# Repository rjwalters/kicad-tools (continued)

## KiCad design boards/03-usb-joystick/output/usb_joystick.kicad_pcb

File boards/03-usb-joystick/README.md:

# USB Joystick Controller Demo

This demo demonstrates the kicad-tools autorouter by routing a USB game controller PCB
with mixed signal types: USB differential pairs, analog inputs, and digital I/O.

## Quick Start

```bash
# One-command build (recommended)
kct build boards/03-usb-joystick

# Or run specific steps
kct build boards/03-usb-joystick --step schematic
kct build boards/03-usb-joystick --step pcb
kct build boards/03-usb-joystick --step route
kct build boards/03-usb-joystick --step verify

# Preview what would happen
kct build boards/03-usb-joystick --dry-run
```

## Circuit Overview

```
                          +------------------+
    +--------+            |                  |
    | USB-C  |---D+/D--->| MCU (32-pin QFP) |<---[Y1 Crystal]
    |  J1    |---VBUS--->|                  |
    +--------+            |   ATmega32U4    |<---[C1-C4 Decoupling]
                          |                  |
                          +--------+---------+
                                   |
          +------------------------+------------------------+
          |            |           |           |            |
      +---+---+   +----+----+  +---+---+   +---+---+   +---+---+
      | JOY_X |   | JOY_Y   |  | BTN1  |   | BTN2  |   | BTN3  |
      +-------+   +---------+  +-------+   +-------+   +-------+
         Analog Joystick              Tactile Buttons
```

## Components

| Reference | Description | Footprint |
|-----------|-------------|-----------|
| U1 | Microcontroller (ATmega32U4-style) | TQFP-32 7x7mm |
| J1 | USB Type-C Connector | USB-C Receptacle |
| J2 | 2-axis Analog Joystick | 5-pin module |
| SW1-SW4 | Tactile Buttons | 6x6mm SMD |
| Y1 | 16MHz Crystal | HC49 Vertical |
| C1-C4 | Decoupling Capacitors (100nF) | 0402 SMD |

## Signal Types

This design demonstrates routing of different signal classes:

### USB Signals (High Priority)
- **USB_D+, USB_D-**: Differential pair, should be length-matched
- **VBUS**: 5V power from USB host
- **USB_CC1, USB_CC2**: Configuration channel for USB-C

### Analog Signals
- **JOY_X, JOY_Y**: Analog joystick axis outputs (0-VCC)
- **JOY_BTN**: Joystick button (active low)

### Digital Signals
- **BTN1-BTN4**: Button inputs (active low with GND)
- **XTAL1, XTAL2**: Crystal oscillator connections

### Power
- **VCC**: 3.3V/5V regulated power
- **GND**: Ground reference
- **VBUS**: USB 5V input

## Files

| File | Description |
|------|-------------|
| `generate_pcb.py` | Script to generate the unrouted PCB file |
| `generate_schematic.py` | Script to generate the schematic file |
| `route_demo.py` | Thin wrapper that delegates to `generate_design.py:route_pcb()` (Issue #3308) |
| `generate_design.py` | End-to-end design flow (schematic + PCB + route + export); owns the canonical routing recipe |
| `output/usb_joystick.kicad_sch` | Generated schematic |
| `output/usb_joystick.kicad_pcb` | Generated unrouted PCB |
| `output/usb_joystick_routed.kicad_pcb` | Routed PCB output |

## Advanced: Manual Build

For more control over individual steps, you can run Python scripts directly. See [Prerequisites](../README.md#prerequisites-for-manual-build) for environment setup.

### Step 1: Generate the Schematic

```bash
# From repository root (default output)
uv run python boards/03-usb-joystick/generate_schematic.py

# Or specify an output directory (auto-appends filename)
uv run python boards/03-usb-joystick/generate_schematic.py output/

# Or specify an explicit file path
uv run python boards/03-usb-joystick/generate_schematic.py output/usb_joystick.kicad_sch
```

Creates `output/usb_joystick.kicad_sch` with all components and wiring.

### Step 2: Generate the PCB

```bash
# From repository root
uv run python boards/03-usb-joystick/generate_pcb.py
```

Creates `output/usb_joystick.kicad_pcb` with all components placed and nets defined.

### Step 3: Run the Autorouter

```bash
# From repository root
uv run python boards/03-usb-joystick/route_demo.py
```

Issue #3308 (June 2026): `route_demo.py` is a thin wrapper that
delegates to `generate_design.py:route_pcb()`.  This guarantees the
demo recipe and the end-to-end build recipe share a single
implementation -- they cannot drift again.  `kct build --step route`
also invokes `route_demo.py` (see `_run_step_route` in
`src/kicad_tools/cli/build_cmd.py`), so all three entry points
(``route_demo.py``, ``kct build --step route``, ``generate_design.py``)
now produce the same routed output.

This:
1. Loads the unrouted PCB
2. Configures net classes (USB gets high priority)
3. Routes signal nets (power nets are skipped, assuming planes)
4. Saves the result to `output/usb_joystick_routed.kicad_pcb`

**Note:** This is a challenging routing problem with a dense 32-pin QFP and multiple
signal types. The autorouter demonstrates its capabilities but may not complete all
routes on a 2-layer board. This is realistic for complex designs requiring manual
intervention or additional layers.

### Step 4: View in KiCad (Optional)

Open `usb_joystick_routed.kicad_pcb` in KiCad to visualize the routes.

## Net Class Configuration

The demo configures net classes for priority-based routing:

```python
net_class_map = create_net_class_map(
    power_nets=["VCC", "VBUS", "GND"],  # Highest priority
    high_speed_nets=["USB_D+", "USB_D-"],  # USB differential pair
    clock_nets=["XTAL1", "XTAL2"],  # Crystal oscillator
)
```

This ensures:
1. Power nets route first (if not skipped)
2. USB differential pair routes early for best path
3. Crystal traces stay short
4. Button/joystick signals route last

## Design Considerations

### USB Routing
- D+ and D- should be routed as a differential pair
- Keep traces short and matched in length
- Avoid sharp bends (use 45-degree angles)

### Analog Signals
- JOY_X and JOY_Y carry analog voltages
- Keep away from high-speed digital signals
- Consider guard traces if noise is an issue

### Crystal Routing
- XTAL1 and XTAL2 should be short
- Place crystal close to MCU pins
- Avoid routing other signals under crystal

### Decoupling Capacitors
- C1-C3 placed close to MCU VCC pins
- C4 on VBUS near USB connector
- Short traces to GND plane

## Customization

### Change Design Rules

```python
rules = DesignRules(
    grid_resolution=0.25,  # Routing grid
    trace_width=0.25,  # Default trace width
    trace_clearance=0.15,  # Minimum clearance
    via_drill=0.3,  # Via drill diameter
    via_diameter=0.6,  # Via pad diameter
)
```

### Route Power Nets

By default, VCC/GND/VBUS are skipped (assuming copper pours). To route them:

```python
skip_nets = []  # Route everything
```

### Adjust Component Placement

Edit `generate_pcb.py` to modify:
- Board dimensions
- Component positions
- Pin assignments

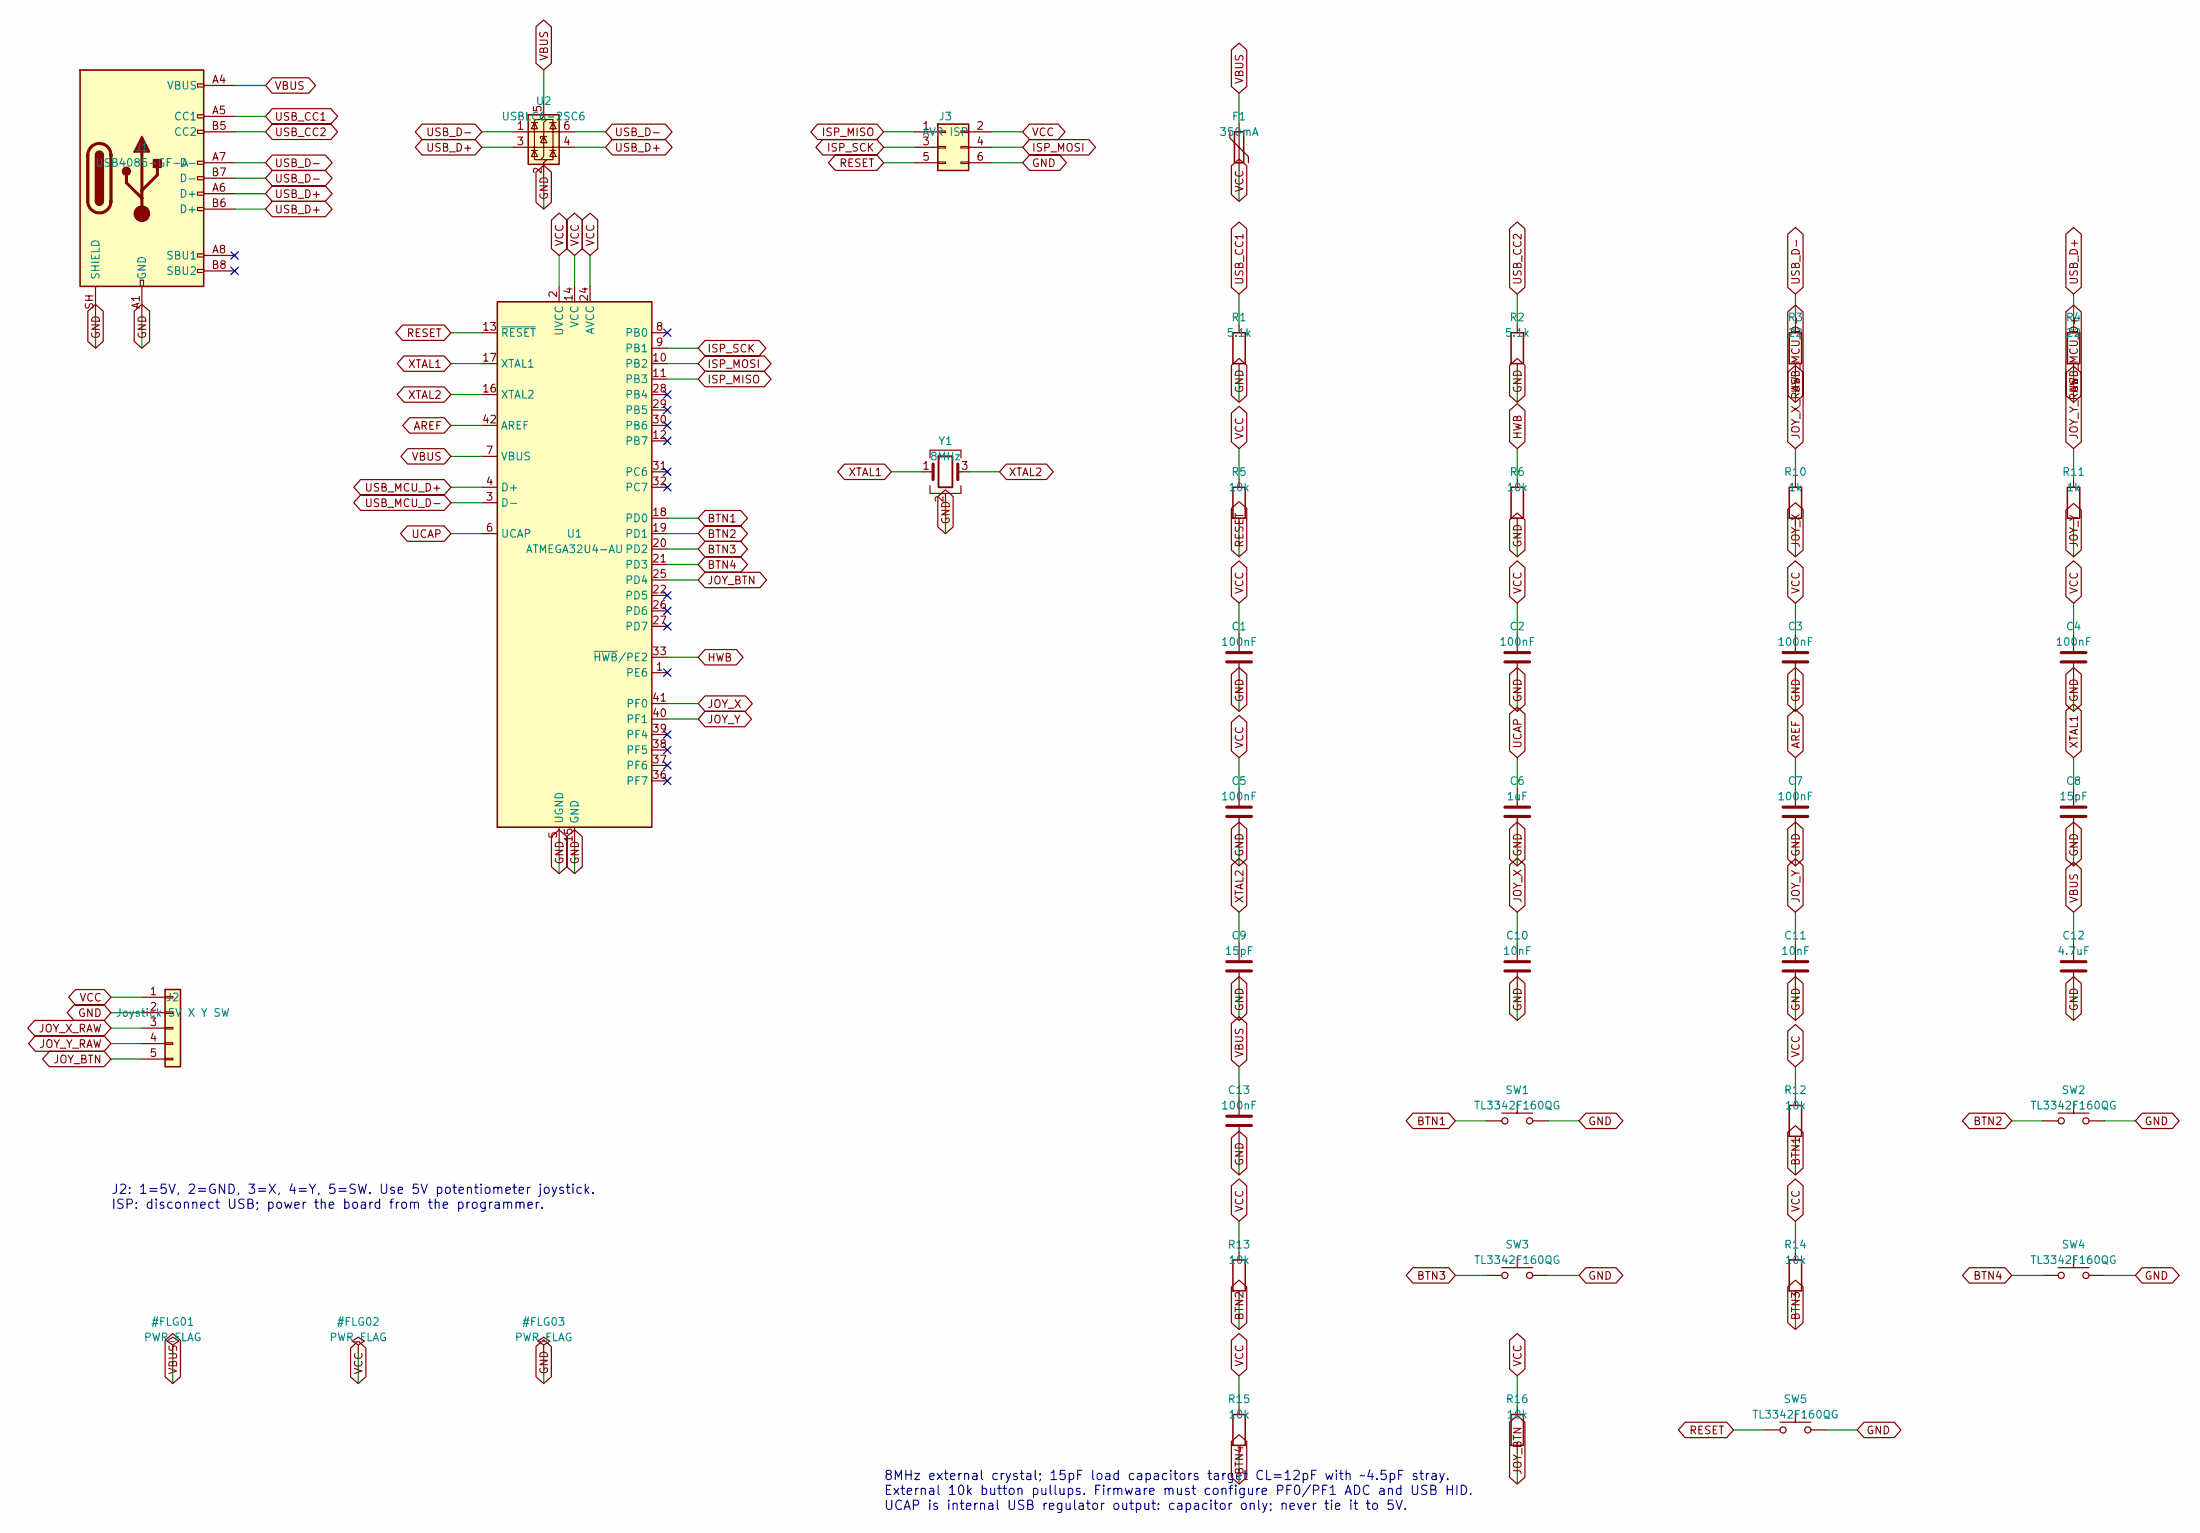
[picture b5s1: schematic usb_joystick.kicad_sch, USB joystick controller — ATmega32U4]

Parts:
C1, C2, C3, C4, C5, C7, C13: 100nF; C_0603_1608Metric; MPN GRM188R71C104KA01D; LCSC C45000
C6: 1uF; C_0603_1608Metric; MPN GRM188R71A105KA61D; LCSC C97888
C8, C9: 15pF; C_0603_1608Metric; MPN GRM1885C1H150JA01D; LCSC C71651
C10, C11: 10nF; C_0603_1608Metric; MPN GRM188R71H103KA01D; LCSC C77053
C12: 4.7uF; C_0603_1608Metric; MPN GRM188R61A475KE15D; LCSC C71633
F1: 350mA; Fuse_1206_3216Metric; MPN 1206L035/16YR; LCSC C126817
J1: USB4085-GF-A; USB_C_Receptacle_GCT_USB4085; MPN USB4085-GF-A; LCSC C7095263
J2: Joystick 5V X Y SW; JST_PH_S5B-PH-SM4-TB_1x05-1MP_P2.00mm_Horizontal; MPN S5B-PH-SM4-TB(LF)(SN); LCSC C265104
J3: AVR ISP; Samtec_TSM-103-01-T-DV; MPN TSM-103-01-T-DV-P-TR; LCSC C21285200
R1, R2: 5.1k; R_0603_1608Metric; MPN RC0603FR-075K1L; LCSC C105580
R3, R4: 22; R_0402_1005Metric; MPN RC0402FR-0722RL; LCSC C114765
R5, R6, R12, R13, R14, R15, R16: 10k; R_0603_1608Metric; MPN RC0603FR-0710KL; LCSC C98220
R10, R11: 1k; R_0603_1608Metric; MPN RC0603FR-071KL; LCSC C22548
SW1, SW2, SW3, SW4, SW5: TL3342F160QG; SW_SPST_TL3342; MPN TL3342F160QG; LCSC C2886898
U1: ATMEGA32U4-AU; TQFP-44_10x10mm_P0.8mm; MPN ATMEGA32U4-AU; LCSC C44854
U2: USBLC6-2SC6; SOT-23-6; MPN USBLC6-2SC6; LCSC C7519
Y1: 8MHz; Crystal_SMD_3225-4Pin_3.2x2.5mm; MPN ECS-80-12-33-JGN-TR; LCSC C2442665

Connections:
AREF: C7.1, U1.42 (AREF)
BTN1: R12.2, SW1.1, U1.18 (PD0)
BTN2: R13.2, SW2.1, U1.19 (PD1)
BTN3: R14.2, SW3.1, U1.20 (PD2)
BTN4: R15.2, SW4.1, U1.21 (PD3)
GND: C1.2, C2.2, C3.2, C4.2, C5.2, C6.2, C7.2, C8.2, C9.2, C10.2, C11.2, C12.2, C13.2, J1.A1 (GND), J1.A12 (GND), J1.B1 (GND), J1.B12 (GND), J1.SH (SHIELD), J2.2, J3.6, R1.2, R2.2, R6.2, SW1.2, SW2.2, SW3.2, SW4.2, SW5.2, U1.5 (UGND), U1.15 (GND), U1.23 (GND), U1.35 (GND), U1.43 (GND), U2.2 (GND), Y1.2 (G), Y1.4 (G)
HWB: R6.1, U1.33 (~HWB/PE2)
ISP_MISO: J3.1, U1.11 (PB3)
ISP_MOSI: J3.4, U1.10 (PB2)
ISP_SCK: J3.3, U1.9 (PB1)
JOY_BTN: J2.5, R16.2, U1.25 (PD4)
JOY_X: C10.1, R10.2, U1.41 (PF0)
JOY_X_RAW: J2.3, R10.1
JOY_Y: C11.1, R11.2, U1.40 (PF1)
JOY_Y_RAW: J2.4, R11.1
RESET: J3.5, R5.2, SW5.1, U1.13 (~RESET)
UCAP: C6.1, U1.6 (UCAP)
USB_CC1: J1.A5 (CC1), R1.1
USB_CC2: J1.B5 (CC2), R2.1
USB_D+: J1.A6 (D+), J1.B6 (D+), R4.1, U2.3 (I/O2), U2.4 (I/O2)
USB_D-: J1.A7 (D-), J1.B7 (D-), R3.1, U2.1 (I/O1), U2.6 (I/O1)
USB_MCU_D+: R4.2, U1.4 (D+)
USB_MCU_D-: R3.2, U1.3 (D-)
VBUS: C12.1, C13.1, F1.1, J1.A4 (VBUS), J1.A9 (VBUS), J1.B4 (VBUS), J1.B9 (VBUS), U1.7 (VBUS), U2.5 (VBUS)
VCC: C1.1, C2.1, C3.1, C4.1, C5.1, F1.2, J2.1, J3.2, R5.1, R12.1, R13.1, R14.1, R15.1, R16.1, U1.2 (UVCC), U1.14 (VCC), U1.24 (AVCC), U1.34 (VCC), U1.44 (AVCC)
XTAL1: C8.1, U1.17 (XTAL1), Y1.1
XTAL2: C9.1, U1.16 (XTAL2), Y1.3

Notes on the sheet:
J2: 1=5V, 2=GND, 3=X, 4=Y, 5=SW. Use 5V potentiometer joystick. ISP: disconnect USB; power the board from the programmer.
8MHz external crystal; 15pF load capacitors target CL=12pF with ~4.5pF stray. External 10k button pullups. Firmware must configure PF0/PF1 ADC and USB HID. UCAP is internal USB regulator output: capacitor only; never tie it to 5V.

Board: 4 copper layers, 38 parts (0 on the bottom side), 27 nets, no tracks yet.

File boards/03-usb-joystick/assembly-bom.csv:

Reference,Value,Manufacturer,MPN,Footprint
U1,ATMEGA32U4-AU,Microchip,ATMEGA32U4-AU,Package_QFP:TQFP-44_10x10mm_P0.8mm
J1,USB4085-GF-A,GCT,USB4085-GF-A,Connector_USB:USB_C_Receptacle_GCT_USB4085
U2,USBLC6-2SC6,STMicroelectronics,USBLC6-2SC6,Package_TO_SOT_SMD:SOT-23-6
F1,350mA,Littelfuse,1206L035/16YR,Fuse:Fuse_1206_3216Metric
Y1,8MHz,ECS,ECS-80-12-33-JGN-TR,Crystal:Crystal_SMD_3225-4Pin_3.2x2.5mm
J2,Joystick 5V X Y SW,JST,S5B-PH-SM4-TB(LF)(SN),Connector_JST:JST_PH_S5B-PH-SM4-TB_1x05-1MP_P2.00mm_Horizontal
J3,AVR ISP,Samtec,TSM-103-01-T-DV-P-TR,Joystick:Samtec_TSM-103-01-T-DV
R1,5.1k,Yageo,RC0603FR-075K1L,Resistor_SMD:R_0603_1608Metric
R2,5.1k,Yageo,RC0603FR-075K1L,Resistor_SMD:R_0603_1608Metric
R3,22,Yageo,RC0402FR-0722RL,Resistor_SMD:R_0402_1005Metric
R4,22,Yageo,RC0402FR-0722RL,Resistor_SMD:R_0402_1005Metric
R5,10k,Yageo,RC0603FR-0710KL,Resistor_SMD:R_0603_1608Metric
R6,10k,Yageo,RC0603FR-0710KL,Resistor_SMD:R_0603_1608Metric
R10,1k,Yageo,RC0603FR-071KL,Resistor_SMD:R_0603_1608Metric
R11,1k,Yageo,RC0603FR-071KL,Resistor_SMD:R_0603_1608Metric
C1,100nF,Murata,GRM188R71C104KA01D,Capacitor_SMD:C_0603_1608Metric
C2,100nF,Murata,GRM188R71C104KA01D,Capacitor_SMD:C_0603_1608Metric
C3,100nF,Murata,GRM188R71C104KA01D,Capacitor_SMD:C_0603_1608Metric
C4,100nF,Murata,GRM188R71C104KA01D,Capacitor_SMD:C_0603_1608Metric
C5,100nF,Murata,GRM188R71C104KA01D,Capacitor_SMD:C_0603_1608Metric
C6,1uF,Murata,GRM188R71A105KA61D,Capacitor_SMD:C_0603_1608Metric
C7,100nF,Murata,GRM188R71C104KA01D,Capacitor_SMD:C_0603_1608Metric
C8,15pF,Murata,GRM1885C1H150JA01D,Capacitor_SMD:C_0603_1608Metric
C9,15pF,Murata,GRM1885C1H150JA01D,Capacitor_SMD:C_0603_1608Metric
C10,10nF,Murata,GRM188R71H103KA01D,Capacitor_SMD:C_0603_1608Metric
C11,10nF,Murata,GRM188R71H103KA01D,Capacitor_SMD:C_0603_1608Metric
C12,4.7uF,Murata,GRM188R61A475KE15D,Capacitor_SMD:C_0603_1608Metric
C13,100nF,Murata,GRM188R71C104KA01D,Capacitor_SMD:C_0603_1608Metric
SW1,TL3342F160QG,E-Switch,TL3342F160QG,Button_Switch_SMD:SW_SPST_TL3342
R12,10k,Yageo,RC0603FR-0710KL,Resistor_SMD:R_0603_1608Metric
SW2,TL3342F160QG,E-Switch,TL3342F160QG,Button_Switch_SMD:SW_SPST_TL3342
R13,10k,Yageo,RC0603FR-0710KL,Resistor_SMD:R_0603_1608Metric
SW3,TL3342F160QG,E-Switch,TL3342F160QG,Button_Switch_SMD:SW_SPST_TL3342
R14,10k,Yageo,RC0603FR-0710KL,Resistor_SMD:R_0603_1608Metric
SW4,TL3342F160QG,E-Switch,TL3342F160QG,Button_Switch_SMD:SW_SPST_TL3342
R15,10k,Yageo,RC0603FR-0710KL,Resistor_SMD:R_0603_1608Metric
R16,10k,Yageo,RC0603FR-0710KL,Resistor_SMD:R_0603_1608Metric
SW5,TL3342F160QG,E-Switch,TL3342F160QG,Button_Switch_SMD:SW_SPST_TL3342

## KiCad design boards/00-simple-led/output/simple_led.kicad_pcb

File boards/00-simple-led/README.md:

# Simple LED (Hello World)

The smallest board in the repo: a 5 V power header, a current-limiting resistor,
and an LED. Three components, three nets. It exists to exercise the *entire*
kicad-tools pipeline — project → schematic → ERC → PCB → zones → route → DRC →
LVS → manufacturing bundle — at the smallest scale where every stage still has
something to do, and its end-to-end result is pinned in CI.

## Quick Start

```bash
# One-command build (recommended)
kct build boards/00-simple-led

# Or run specific steps
kct build boards/00-simple-led --step schematic
kct build boards/00-simple-led --step pcb
kct build boards/00-simple-led --step route
kct build boards/00-simple-led --step verify

# Preview what would happen, touching nothing
kct build boards/00-simple-led --dry-run
```

`kct build` discovers `generate_design.py` generically (see
`src/kicad_tools/cli/build_cmd.py`), so no board-specific registration is
needed. The default manufacturer profile is JLCPCB.

Verify the committed artifacts without rebuilding anything:

```bash
kct check boards/00-simple-led/output/simple_led_routed.kicad_pcb
# Overall:   PASSED   (DRC + ERC + LVS + Manifest)

kct net-status boards/00-simple-led/output/simple_led_routed.kicad_pcb
# Summary: 3 nets total — Complete: 3 (all pads connected)
```

## Circuit Overview

```
    +5V ──── J1.1 ────┬──────────── VCC   (pour)
                      │
                     [R1]
                     330R
                      │
                      ├──────────── LED_ANODE
                      │
                     (D1)  LED, Vf ≈ 2 V
                      │
    GND ──── J1.2 ────┴──────────── GND   (pour)
```

Three nets: **`VCC`**, **`LED_ANODE`**, **`GND`**. `VCC` and `GND` are pour
nets (copper zones); `LED_ANODE` is the single trace-routed signal net — which
is exactly why this board is the cheapest possible end-to-end pipeline test.

### Resistor sizing

```
R = (V_in − V_f) / I = (5 V − 2 V) / 10 mA = 300 Ω  →  330 Ω (nearest E24)
```

330 Ω delivers roughly **9 mA**, which is safe and clearly visible. The
rationale is recorded in `generate_design.py`'s module docstring and under
`decisions:` in `project.kct`.

## Components

| Reference | Description | Value | Footprint | Part | LCSC |
|-----------|-------------|-------|-----------|------|------|
| J1 | Power input header (VCC, GND) | — | `PinHeader_1x02_P2.54mm_Vertical` | ZX-PZ2.54-1-2PZZ | C7501260 |
| R1 | Current-limiting resistor | 330 Ω | `R_0805_2012Metric` | 0805W8F3300T5E | C17630 |
| D1 | Indicator LED | Vf ≈ 2 V | `LED_D5.0mm` | 333-2SURD/S530-A3 | C87271 |

The 5 mm through-hole LED plus the 0805 SMD resistor make this a deliberately
mixed THT/SMD board — see the `decisions:` block in `project.kct`.

## Design Specifications

| Parameter | Value |
|-----------|-------|
| Input Voltage | 5 V |
| LED Forward Voltage | ~2 V |
| Target LED Current | 10 mA (≈9 mA actual with 330 Ω) |
| Board Size | 25 mm × 20 mm |
| Layers | 2 |
| Nets | 3 (`VCC`, `LED_ANODE`, `GND`) |
| Target Fab | JLCPCB |

## Files

| File | Description |
|------|-------------|
| `generate_design.py` | The recipe: builds project, schematic, PCB, routes, runs ERC/DRC/LVS, exports the manufacturing bundle. Accepts an optional output directory as `argv[1]`. |
| `project.kct` | Project specification — intent, requirements, component list, BOM/LCSC mapping, and the `decisions:` log. |
| `output/simple_led.kicad_sch` | Generated schematic |
| `output/simple_led.kicad_pcb` | Generated unrouted PCB (+ `.kicad_pro`, `.kicad_prl`) |
| `output/simple_led_routed.kicad_pcb` | Routed PCB (+ `.kicad_pro`, `.kicad_prl`, `.kicad_dru` design rules) |
| `output/lvs.json` | Copper + label LVS report; `clean: true` on the committed board |
| `package_release.py` | Rebuilds the shipped package below through `kct readiness --generate`; run it after `generate_design.py` changes the PCB. |
| `output/manufacturing/` | Full fab bundle — see below |
| `output/readiness.json`, `output/readiness/` | Hash-bound readiness verdict and its gate evidence |

The `output/manufacturing/` bundle contains `gerbers/gerbers.zip`,
`bom_jlcpcb.csv`, `cpl_jlcpcb.csv`, `kicad_project.zip`, `manifest.json`,
`README.txt`, `report.md`, `report.pdf`, `schematic.pdf`,
`assembly-front.pdf`/`assembly-back.pdf`, the sign-off evidence
`check-report.json` and `native-drc.json`, the supplier review
`procurement-review.md`, and `images/` (front/back/copper/assembly renders
plus per-layer PNGs and the schematic render). `output/manufacturing.zip`
archives the whole bundle.

`output/board.json` is **not** committed — it is the public data contract
emitted on demand by `kct board-metrics`, which CI runs against a temporary
regeneration (below).

## Regenerating: always target a scratch directory

```bash
uv run python boards/00-simple-led/generate_design.py /tmp/board00
```

**Do not regenerate into the committed `output/` tree.** `generate_design.py`
falls back to `<board_dir>/output` when no `argv[1]` is given, which rewrites
tracked artifacts; `tests/conftest.py` additionally fails the test suite if
tracked files under `boards/**/output/` are modified during a test run. Passing
an explicit scratch directory is exactly what CI does, and it keeps a
verification run out of your diff.

If you *intend* to refresh the committed artifacts, do it as a deliberate,
reviewed change — not as a side effect of checking that the recipe still works.

## CI gate: `Board 00 End-to-End`

The `Board 00 End-to-End` job in `.github/workflows/ci.yml` runs on pushes to
`main` and on pull requests targeting `main`, inside a `kicad/kicad:10.0`
container. It is the contract this board must keep:

1. `uv sync --frozen --extra dev --python 3.12`, then `uv run kct build-native`
   — `uv sync` does not build the C++ router extension, and without it routing
   falls back to slow pure Python.
2. Regenerate into a clean temp directory:
   `uv run python boards/00-simple-led/generate_design.py /tmp/board00-ci`.
   The committed `output/` tree is never touched.
3. `uv run kct check /tmp/board00-ci/simple_led_routed.kicad_pcb` must print
   `Overall: PASSED` — a grep on `^Overall:[[:space:]]+PASSED` gates the build,
   so DRC **and** ERC **and** LVS **and** Manifest must all pass. No
   `--allow-incomplete`.
4. Mirror the regen into a `<board_dir>/output/` shape and emit `board.json`
   with `uv run kct board-metrics /tmp/board00-staging/00-simple-led`.
5. `scripts/ci/check_net_status.py` asserts plane-net completion — the raw
   `total_unconnected_pads` count, so a floating `VCC`/`GND` pad cannot hide
   behind the advisory power/plane classification (#4531).
6. `scripts/ci/check_board_00_e2e.py` asserts the artifact contract: every
   expected artifact present (schematic, PCB, routed PCB, `lvs.json`,
   `manufacturing/manifest.json`), `lvs.json` `clean: true`, and `board.json`
   reporting `status: ok`, `drc_violations: 0`, `lvs_clean: true`.

Note that the gate re-derives DRC from scratch; no `drc_report.json` is
committed (the old unproduced snapshots were removed in issue #7190, and
export preflight no longer trusts a report that is not bound to the PCB's
content). The recipe's own fast-fail gates (partial-route
detection, `write_lvs_report(require_clean=True)`) run inside step 2. Whether
this job is a *required* status check on `main` is a separate repo-admin
setting — it landed advisory, per the note in the job's own comment block.

## Why This Board?

It is the minimum viable proof that the toolchain works end to end. One signal
net means routing can never be the interesting failure — so when this job goes
red, the break is in the pipeline (schematic emission, zone creation, LVS,
export, manifest freshness), not in the router. That makes it the fastest
possible canary and the right place to start reading if you are new to the
repo.

## Related

- [`../README.md`](../README.md) — the board index and status table
- [01-voltage-divider](../01-voltage-divider/) — next step up: 4 components, a divider, and the same pipeline
- [02-charlieplex-led](../02-charlieplex-led/) — where routing starts to be the hard part

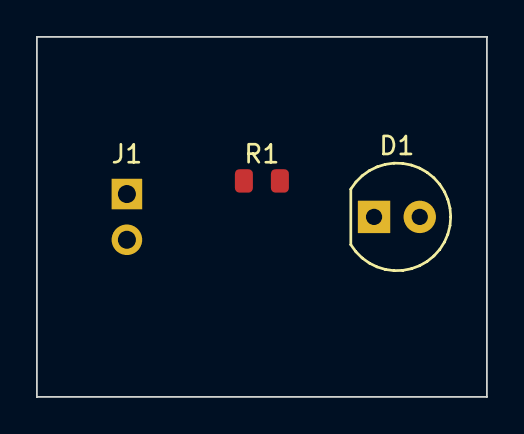
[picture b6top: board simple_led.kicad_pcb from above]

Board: 2 copper layers, 25.0 x 20.0 mm, 3 parts (0 on the bottom side), 3 nets, no tracks yet.

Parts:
D1: LED; LED_D5.0mm
J1: PWR; PinHeader_1x02_P2.54mm_Vertical
R1: 330; R_0805_2012Metric

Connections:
GND: D1.1 (K), J1.2
LED_ANODE: D1.2 (A), R1.2
VCC: J1.1, R1.1

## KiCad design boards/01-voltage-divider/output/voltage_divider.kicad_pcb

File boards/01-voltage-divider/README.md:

# Voltage Divider Demo

This demo demonstrates the complete kicad-tools workflow by creating the simplest possible PCB: a 4-component voltage divider.

## Quick Start

```bash
# One-command build (recommended)
kct build boards/01-voltage-divider

# Or run specific steps
kct build boards/01-voltage-divider --step schematic
kct build boards/01-voltage-divider --step pcb
kct build boards/01-voltage-divider --step route
kct build boards/01-voltage-divider --step verify

# Preview what would happen
kct build boards/01-voltage-divider --dry-run
```

## Circuit Overview

```
    +5V ─────┬─────────── J1 (Input)
             │
            [R1]
            10k
             │
    VOUT ────┼─────────── J2 (Output)
             │
            [R2]
            10k
             │
    GND ─────┴─────────── (Common)
```

Two 10k resistors divide the 5V input to produce 2.5V output (50% division ratio).

## Components

| Reference | Description | Footprint |
|-----------|-------------|-----------|
| J1 | Input connector (5V, GND) | 2.54mm pin header |
| J2 | Output connector (VOUT, GND) | 2.54mm pin header |
| R1 | Voltage divider (top) | 0805 SMD 10k |
| R2 | Voltage divider (bottom) | 0805 SMD 10k |

## Files

| File | Description |
|------|-------------|
| `generate_design.py` | Script to generate schematic, PCB, and route |
| `project.kct` | Project specification with requirements |
| `output/voltage_divider.kicad_sch` | Generated schematic |
| `output/voltage_divider.kicad_pcb` | Generated unrouted PCB |
| `output/voltage_divider_routed.kicad_pcb` | Routed PCB |

## Advanced: Manual Build

For more control, run the Python script directly. See [Prerequisites](../README.md#prerequisites-for-manual-build) for environment setup.

### Step 1: Generate the Design

```bash
# From repository root
uv run python boards/01-voltage-divider/generate_design.py
```

This creates:
- Schematic with all components and nets
- PCB with components placed on 30mm x 25mm board
- Routed PCB with all traces complete

### Step 2: Verify Output (Optional)

```bash
# Check for DRC violations
kct check output/voltage_divider_routed.kicad_pcb --mfr jlcpcb

# Generate BOM
kct bom output/voltage_divider.kicad_sch --format csv
```

### Step 3: View in KiCad (Optional)

Open `output/voltage_divider_routed.kicad_pcb` in KiCad to visualize the design.

## Design Specifications

| Parameter | Value |
|-----------|-------|
| Input Voltage | 5V |
| Output Voltage | 2.5V |
| Division Ratio | 0.5 (50%) |
| Board Size | 30mm x 25mm |
| Layers | 2 |
| Target Fab | JLCPCB |

## Why This Board?

This is the **simplest possible validation project** for kicad-tools. It exercises:

1. **Schematic Generation** - Creating symbols, wires, and net labels
2. **PCB Creation** - Placing footprints and defining the board outline
3. **Autorouting** - Connecting all nets with copper traces
4. **DRC Checking** - Validating against manufacturer rules

If the voltage divider routes successfully, the core workflow is verified.

## Related

- [02-charlieplex-led](../02-charlieplex-led/) - More complex routing challenge
- [03-usb-joystick](../03-usb-joystick/) - Mixed-signal design
- [04-stm32-devboard](../04-stm32-devboard/) - Programmatic schematic generation

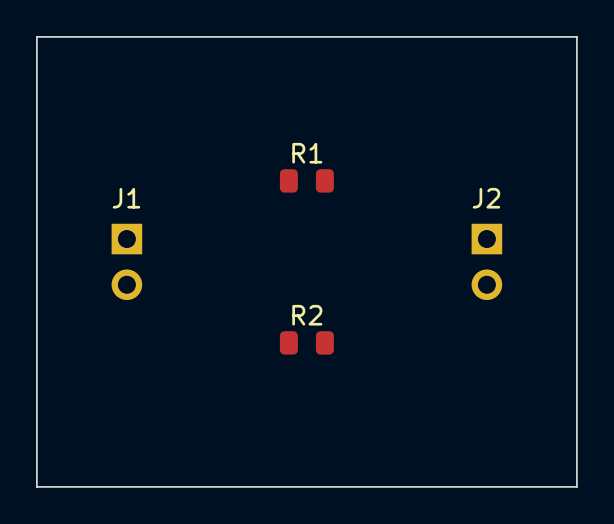
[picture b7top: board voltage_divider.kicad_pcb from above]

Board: 2 copper layers, 30.0 x 25.0 mm, 4 parts (0 on the bottom side), 3 nets, no tracks yet.

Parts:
J1: IN; PinHeader_1x02_P2.54mm_Vertical
J2: OUT; PinHeader_1x02_P2.54mm_Vertical
R1, R2: 10k; R_0805_2012Metric

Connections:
GND: J1.2, J2.2, R2.2
VIN: J1.1, R1.1
VOUT: J2.1, R1.2, R2.1

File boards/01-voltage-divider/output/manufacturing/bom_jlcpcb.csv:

Comment,Designator,Footprint,LCSC Part #
10k,"R1,R2",Resistor_SMD:R_0805_2012Metric,C17414
IN,J1,Connector_PinHeader_2.54mm:PinHeader_1x02_P2.54mm_Vertical,C7501260
OUT,J2,Connector_PinHeader_2.54mm:PinHeader_1x02_P2.54mm_Vertical,C7501260

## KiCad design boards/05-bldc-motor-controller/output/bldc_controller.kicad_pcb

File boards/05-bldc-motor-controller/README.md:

# Sensored BLDC Controller

Revision B is a real 42-component, 70 × 90 mm, four-layer small-motor controller:
ATmega328P-AU, DRV8313PWPR integrated triple half bridge, and TPS7A1650DGNR
5 V supply. It includes reverse-input protection, fuse, transient clamp,
charge-pump capacitors, current comparator, Hall inputs, AVR ISP, RUN switch
input, speed trimmer and working commutation firmware.

Start at 12 V with a 0.5 A current-limited bench supply, an unloaded motor,
RUN open and the speed input at its measured low-voltage end. The initial
phase-current target is 0.5 A; the nominal comparator trip is 1 A and firmware
caps duty at 25%. Physical motor operation and thermal performance have not
yet been measured. Read [HARDWARE.md](redesign/HARDWARE.md) before assembly,
programming or power-up; it contains all connector pinouts and verified BOM identities.

Generate the real circuit and reviewed route, run native refill/DRC/ERC and
manufacturer/LVS gates, and export its assembly bundle:

```sh
uv run python boards/05-bldc-motor-controller/design.py [output-directory]
```

Failed reconstruction leaves the preceding output intact. The route is explicit
reviewed copper in `redesign/routing.json`, guarded by a hash of the actual
component/pad/placement/net geometry. It combines automatic routing with manual
physical corrections; changing circuit geometry requires a new route and fresh
gates. No synthetic routing pads are present in the generated board.

The active revision-B recipe calls the generic physical power-stitch transaction
before its final native and manufacturing gates. It accepts existing complete
power copper or a safely completed candidate after real refill, preserving all
previous pad bonds and rejecting new native findings. Its retained `readiness/stitch`
ledger contains saved, refilled-before, proposed and refilled-candidate bytes,
native reports and physical pad components. Failed stage evidence is retained in
the `bldc-power-stitch-*` temporary directory named by the error.

Fresh reconstruction at main `7368bf597eaefb2dbe171f79db3c3216843a2ae6` already had
zero native opens/errors and clean copper LVS (149 bound pads); the historical
57-open legacy audit does not describe this active recipe. The generic split-plane
regression in `tests/fixtures/stitch-5388` demonstrates why added vias alone cannot
prove completion. Issue #4410 remains open for its later routing/Kelvin/QFN phases.

The manufacturing bundle has 36 SMT placements; hand-solder J1–J5 and RV1.
Solder both driver/regulator exposed pads. Use the included local symbol and
footprint libraries, native drawings, BOM/CPL and firmware. Fresh reconstruction
passed native KiCad DRC/ERC with zero findings and manufacturer checks with
zero errors or warnings. These fabrication checks do not replace motor and
thermal bench validation.

The original DRV8301 circuit is retained in [legacy_drv8301](legacy_drv8301/ARCHIVE.md)
as an electrically invalid historical regression fixture, documented in
[issue #4993](https://github.com/2AMLogic/kicad-tools/issues/4993). Its generator
writes `regression-output`; the default command above builds revision B.

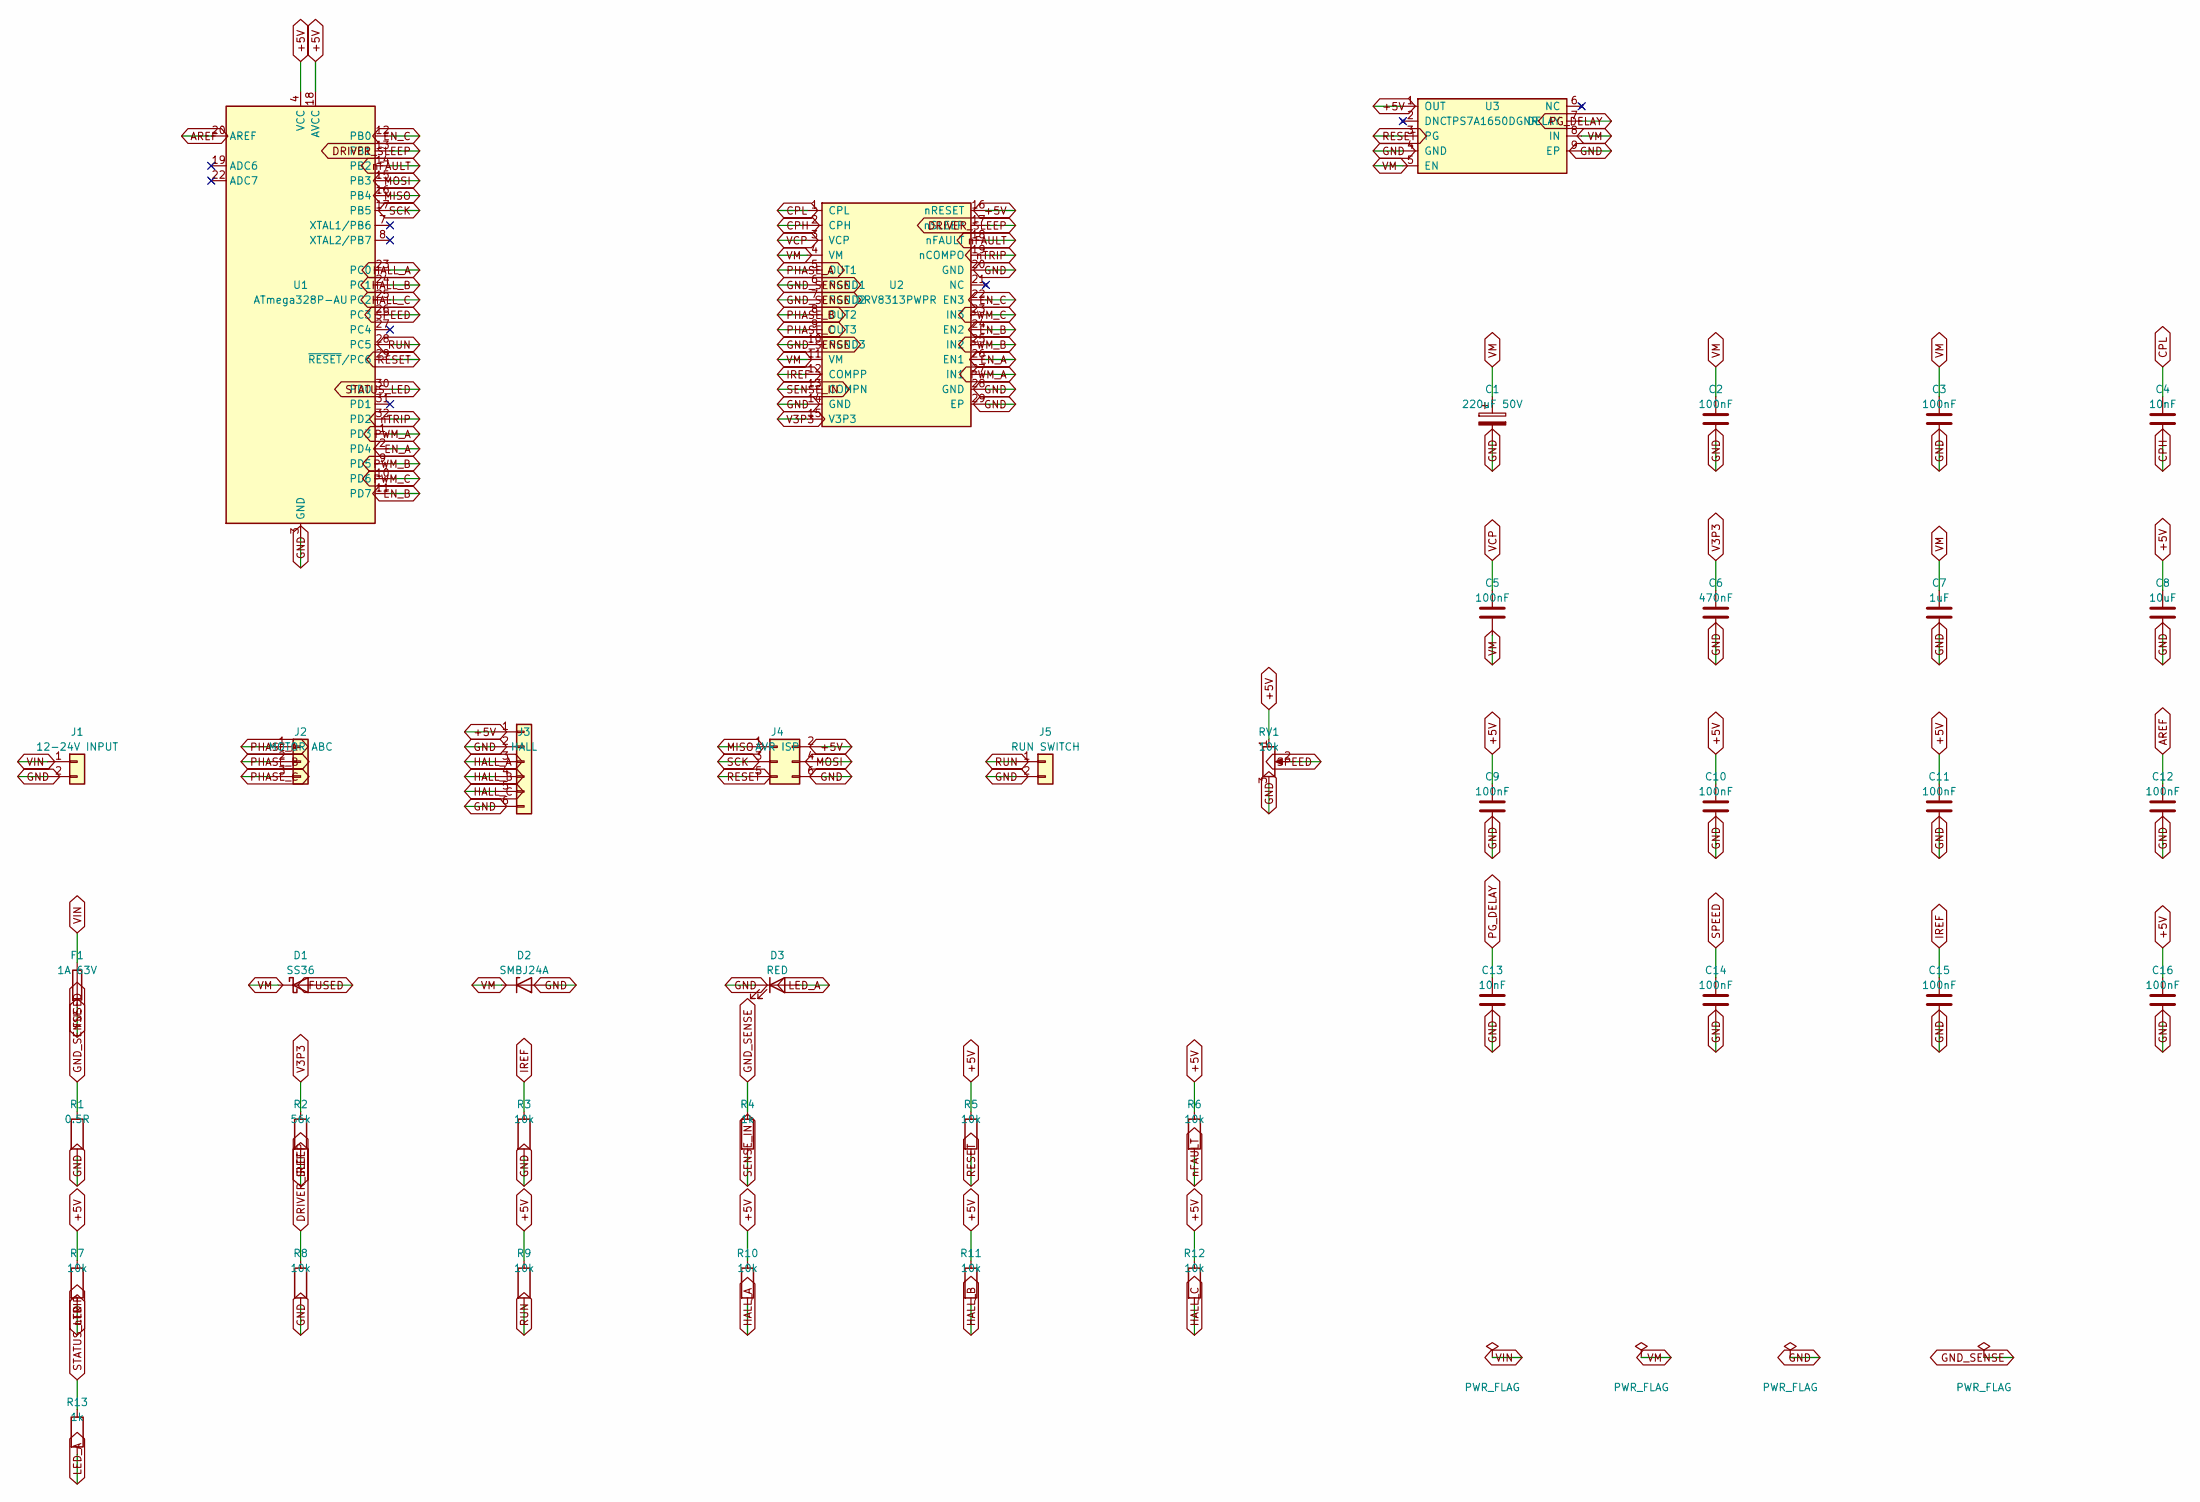
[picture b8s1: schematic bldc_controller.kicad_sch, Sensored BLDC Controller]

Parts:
C1: 220uF 50V; CP_Elec_8x10.5_PolarityMark; MPN EEEFT1H221AP; LCSC C178594
C2, C3, C5, C9, C10, C11, C12, C14, C15, C16: 100nF; C_0805_2012Metric; MPN CC0805KRX7R9BB104; LCSC C49678
C4, C13: 10nF; C_0805_2012Metric; MPN CL21B103KBANNNC; LCSC C1710
C6: 470nF; C_0805_2012Metric; MPN CL21B474KBFNNNE; LCSC C13967
C7: 1uF; C_0805_2012Metric; MPN CL21B105KBFNNNE; LCSC C28323
C8: 10uF; C_0805_2012Metric; MPN CL21A106KAYNNNE; LCSC C15850
D1: SS36; D_SMA; MPN SS36; LCSC C16015
D2: SMBJ24A; D_SMB; MPN SMBJ24A; LCSC C224017
D3: RED; LED_0805_2012Metric; MPN NCD0805R1; LCSC C84256
F1: 1A 63V; Fuse_1206_3216Metric; MPN SF-1206S100-2; LCSC C3167176
J1: 12-24V INPUT; PinHeader_1x02_P2.54mm_Vertical; MPN ZX-PZ2.54-1-2PZZ; LCSC C7501260
J2: MOTOR ABC; PinHeader_1x03_P2.54mm_Vertical; MPN 2.54-1*3P; LCSC C49257
J3: HALL; PinHeader_1x06_P2.54mm_Vertical; MPN 2.54-1*6P; LCSC C37208
J4: AVR ISP; PinHeader_2x03_P2.54mm_Vertical; MPN 2.54-2*3P; LCSC C65114
J5: RUN SWITCH; PinHeader_1x02_P2.54mm_Vertical; MPN ZX-PZ2.54-1-2PZZ; LCSC C7501260
R1: 0.5R; R_2512_6332Metric; MPN WSL2512R5000FEA; LCSC C511023
R2: 56k; R_0805_2012Metric; MPN 0805W8F5602T5E; LCSC C17756
R3, R5, R6, R7, R8, R9, R10, R11, R12: 10k; R_0805_2012Metric; MPN 0805W8F1002T5E; LCSC C17414
R4, R13: 1k; R_0805_2012Metric; MPN 0805W8F1001T5E; LCSC C17513
RV1: 10k; Potentiometer_Bourns_3296W_Vertical; MPN 3296W-1-103LF; LCSC C34846
U1: ATmega328P-AU; TQFP-32_7x7mm_P0.8mm; MPN ATMEGA328P-AU; LCSC C14877
U2: DRV8313PWPR; TI_PWP0028C_EP3.4x9.7_Mask3.1x5.18_ThermalVias; MPN DRV8313PWPR; LCSC C92482
U3: TPS7A1650DGNR; HVSSOP-8-1EP_3x3mm_P0.65mm_EP1.57x1.89mm_ThermalVias; MPN TPS7A1650DGNR; LCSC C468238

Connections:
+5V: C8.1, C9.1, C10.1, C11.1, C16.1, J3.1, J4.2, R5.1, R6.1, R7.1, R9.1, R10.1, R11.1, R12.1, RV1.1, U1.4 (VCC), U1.6 (VCC), U1.18 (AVCC), U2.16 (nRESET), U3.1 (OUT)
AREF: C12.1, U1.20 (AREF)
CPH: C4.2, U2.2 (CPH)
CPL: C4.1, U2.1 (CPL)
DRIVER_SLEEP: R8.1, U1.13 (PB1), U2.17 (nSLEEP)
EN_A: U1.2 (PD4), U2.26 (EN1)
EN_B: U1.11 (PD7), U2.24 (EN2)
EN_C: U1.12 (PB0), U2.22 (EN3)
FUSED: D1.2 (A), F1.2
HALL_A: J3.3, R10.2, U1.23 (PC0)
HALL_B: J3.4, R11.2, U1.24 (PC1)
HALL_C: J3.5, R12.2, U1.25 (PC2)
IREF: C15.1, R2.2, R3.1, U2.12 (COMPP)
LED_A: D3.2 (A), R13.2
MISO: J4.1, U1.16 (PB4)
MOSI: J4.4, U1.15 (PB3)
PG_DELAY: C13.1, U3.7 (DELAY)
PHASE_A: J2.1, U2.5 (OUT1)
PHASE_B: J2.2, U2.8 (OUT2)
PHASE_C: J2.3, U2.9 (OUT3)
PWM_A: U1.1 (PD3), U2.27 (IN1)
PWM_B: U1.9 (PD5), U2.25 (IN2)
PWM_C: U1.10 (PD6), U2.23 (IN3)
RESET: J4.5, R5.2, U1.29 (~RESET/PC6), U3.3 (PG)
RUN: J5.1, R9.2, U1.28 (PC5)
SCK: J4.3, U1.17 (PB5)
SENSE_IN: R4.2, U2.13 (COMPN)
SPEED: C14.1, RV1.2, U1.26 (PC3)
STATUS_LED: R13.1, U1.30 (PD0)
V3P3: C6.1, R2.1, U2.15 (V3P3)
VCP: C5.1, U2.3 (VCP)
nFAULT: R6.2, U1.14 (PB2), U2.18 (nFAULT)
nTRIP: R7.2, U1.32 (PD2), U2.19 (nCOMPO)

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
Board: 4 copper layers, 42 parts (0 on the bottom side), 37 nets, no tracks yet.

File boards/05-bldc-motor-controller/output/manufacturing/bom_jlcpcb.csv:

Comment,Designator,Footprint,LCSC Part #
0.5R,R1,Resistor_SMD:R_2512_6332Metric,C511023
100nF,"C10,C11,C12,C14,C15,C16,C2,C3,C5,C9",Capacitor_SMD:C_0805_2012Metric,C49678
10k,RV1,Potentiometer_THT:Potentiometer_Bourns_3296W_Vertical,C34846
10k,"R10,R11,R12,R3,R5,R6,R7,R8,R9",Resistor_SMD:R_0805_2012Metric,C17414
10nF,"C13,C4",Capacitor_SMD:C_0805_2012Metric,C1710
10uF,C8,Capacitor_SMD:C_0805_2012Metric,C15850
12-24V INPUT,J1,Connector_PinHeader_2.54mm:PinHeader_1x02_P2.54mm_Vertical,C7501260
1A 63V,F1,Fuse:Fuse_1206_3216Metric,C3167176
1k,"R13,R4",Resistor_SMD:R_0805_2012Metric,C17513
1uF,C7,Capacitor_SMD:C_0805_2012Metric,C28323
220uF 50V,C1,board05_revB:CP_Elec_8x10.5_PolarityMark,C178594
470nF,C6,Capacitor_SMD:C_0805_2012Metric,C13967
56k,R2,Resistor_SMD:R_0805_2012Metric,C17756
ATmega328P-AU,U1,Package_QFP:TQFP-32_7x7mm_P0.8mm,C14877
AVR ISP,J4,Connector_PinHeader_2.54mm:PinHeader_2x03_P2.54mm_Vertical,C65114
DRV8313PWPR,U2,board05_revB:TI_PWP0028C_EP3.4x9.7_Mask3.1x5.18_ThermalVias,C92482
HALL,J3,Connector_PinHeader_2.54mm:PinHeader_1x06_P2.54mm_Vertical,C37208
MOTOR ABC,J2,Connector_PinHeader_2.54mm:PinHeader_1x03_P2.54mm_Vertical,C49257
RED,D3,LED_SMD:LED_0805_2012Metric,C84256
RUN SWITCH,J5,Connector_PinHeader_2.54mm:PinHeader_1x02_P2.54mm_Vertical,C7501260
SMBJ24A,D2,Diode_SMD:D_SMB,C224017
SS36,D1,Diode_SMD:D_SMA,C16015
TPS7A1650DGNR,U3,Package_SO:HVSSOP-8-1EP_3x3mm_P0.65mm_EP1.57x1.89mm_ThermalVias,C468238
